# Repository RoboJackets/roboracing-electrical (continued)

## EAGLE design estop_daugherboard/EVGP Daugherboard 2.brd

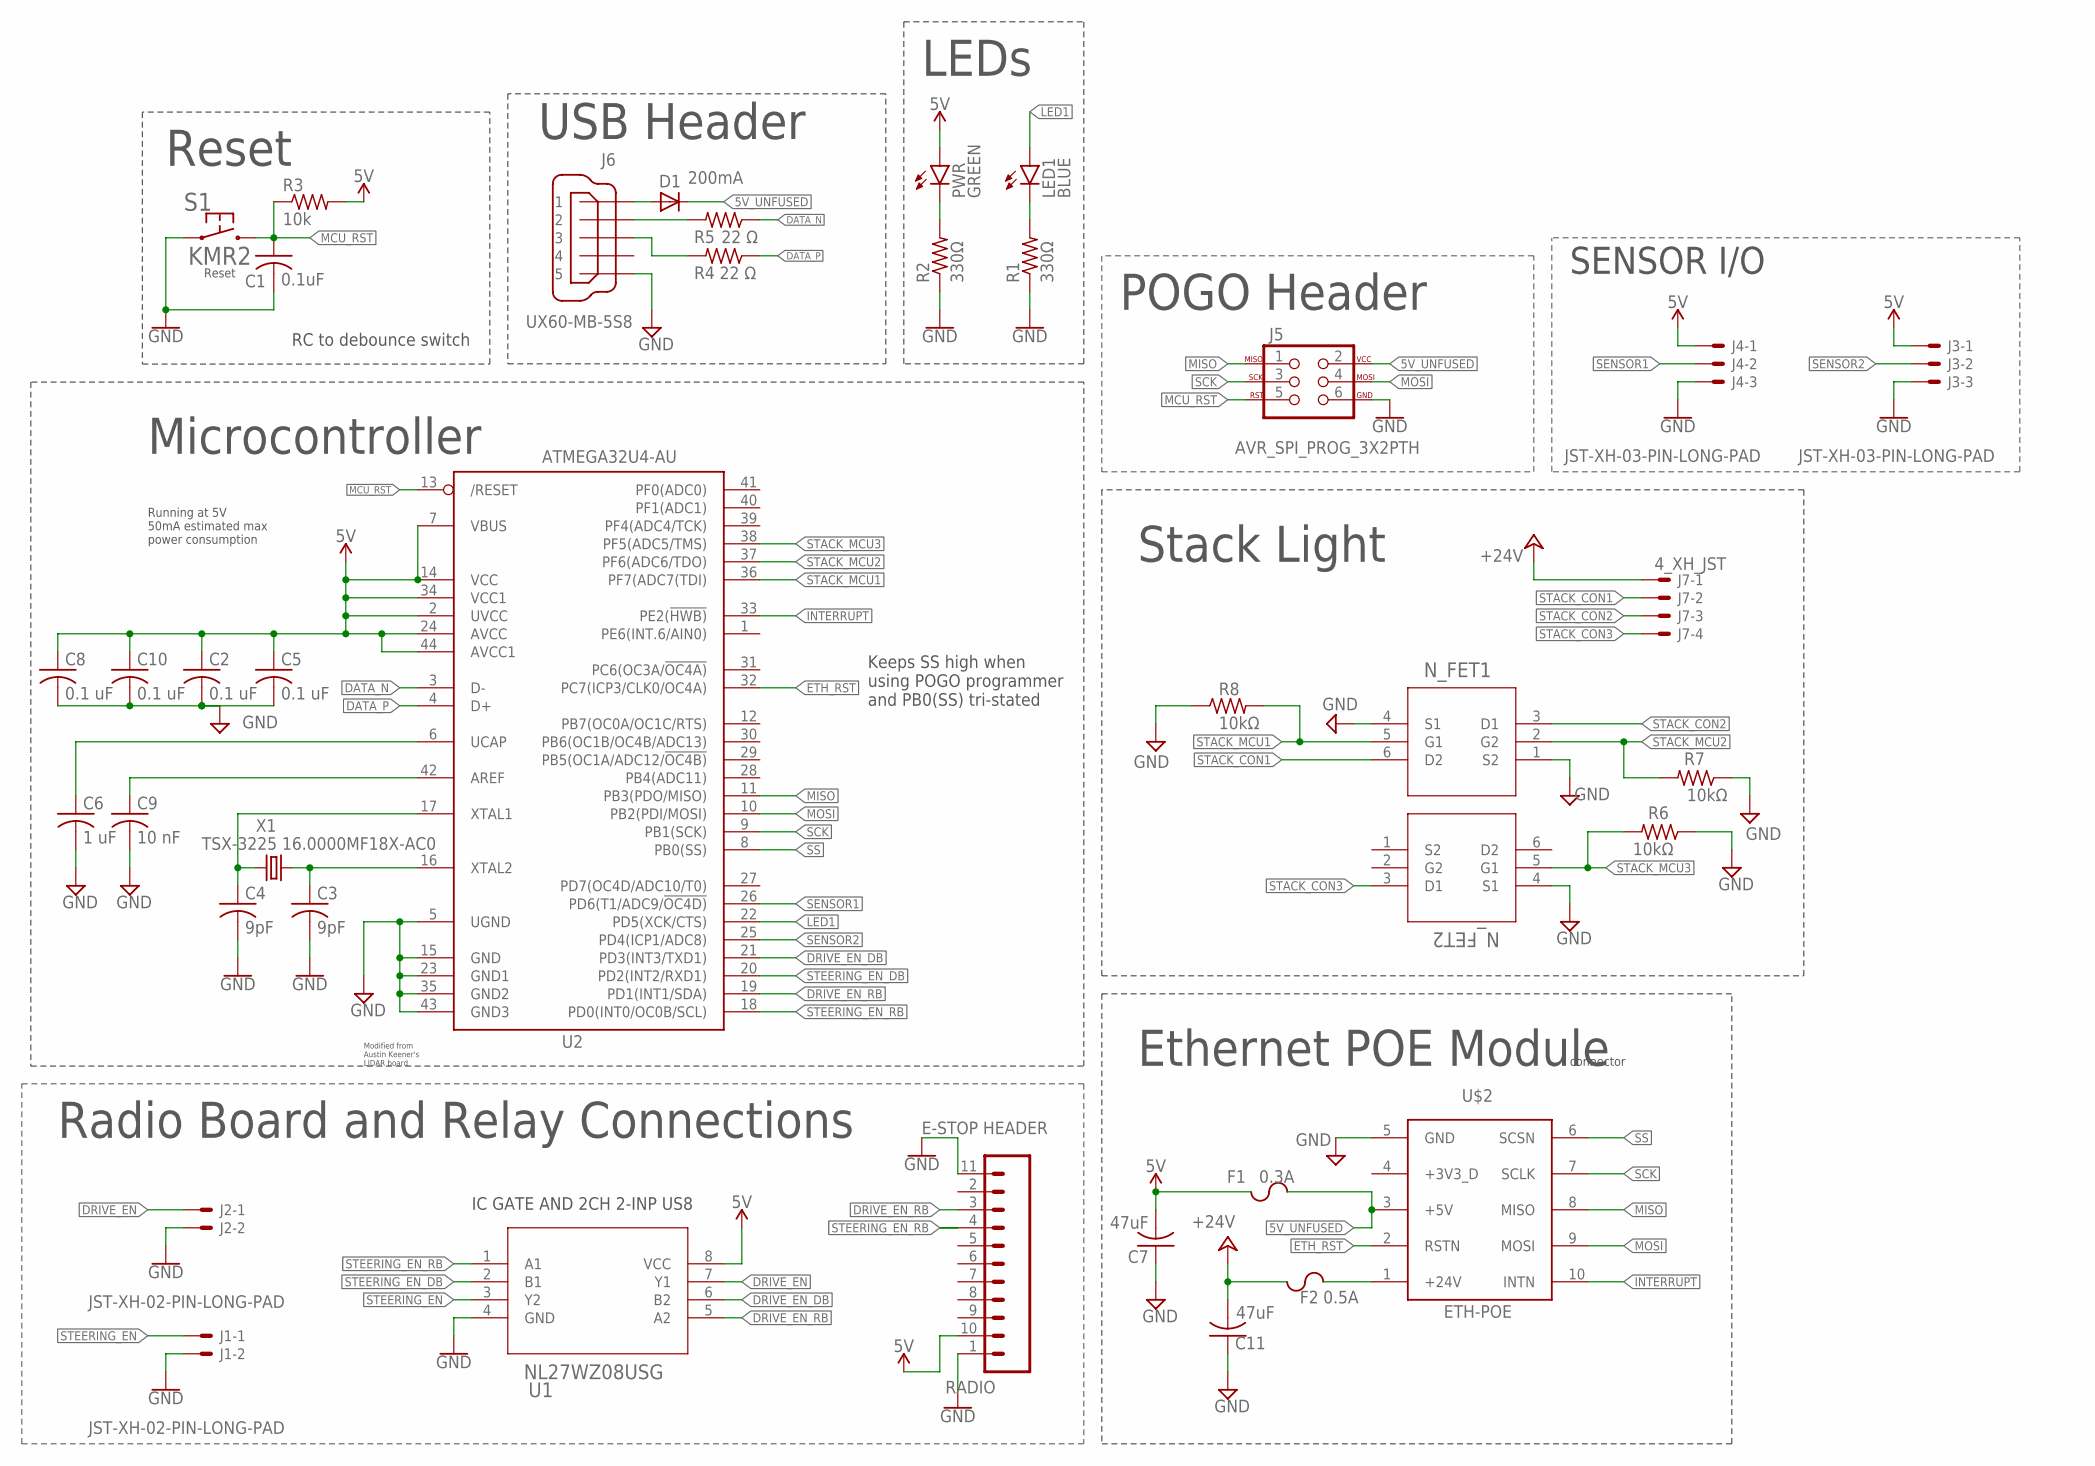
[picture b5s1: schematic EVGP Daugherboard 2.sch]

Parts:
C1: 0.1uF; C0603
C2, C5, C8, C10: 0.1 uF; C0603
C3, C4: 9pF; C0603
C6: 1 uF; C0603
C7, C11: 47uF; C1206
C9: 10 nF; C0603
D1: 200mA; SOD323-R
F1: 0.3A; F1206
F2: 0.5A; F1206
J1, J2: JST-XH-02-PIN-LONG-PAD; JST-XH-02-PACKAGE-LONG-PAD
J3, J4: JST-XH-03-PIN-LONG-PAD; JST-XH-03-PACKAGE-LONG-PAD
J5: AVR_SPI_PROG_3X2PTH; 2X3
J6: UX60-MB-5S8
J7: 4_XH_JST; JST-XH-04-PACKAGE-LONG-PAD
LED1: BLUE; CHIP-LED0603
PWR: GREEN; CHIP-LED0603
Q1: N_FET2; SOT-363
Q2: N_FET1; SOT-363
R1, R2: 330Ω; R0603
R3: 10k; R0603
R4, R5: 22 Ω; R0603
R6, R7, R8: 10kΩ; R0603
RADIO: E-STOP HEADER; RADIO_V1.3
S1: KMR2
U1: NL27WZ08USG; US8_2P40X2P10
U2: ATMEGA32U4-AU; TQFP44
U$2: ETH-POE; HDRVR10W64P4000X254_2X5_1016X508X254B
X1: TSX-3225 16.0000MF18X-AC0; XTAL-3.2X2.5

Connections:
5V: C2.1, C5.1, C7.2, C8.1, C10.1, F1.1, J3.1, J4.1, PWR.A, R3.2, RADIO.10 (5V), U1.8 (VCC), U2.2 (UVCC), U2.7 (VBUS), U2.14 (VCC), U2.24 (AVCC), U2.34 (VCC1), U2.44 (AVCC1)
5V_UNFUSED: D1.C, F1.2, J5.2, U$2.3 (+5V)
24V_UNFUSED: F2.2, U$2.1 (+24V)
+24V: C11.2, F2.1, J7.1
AREF: C9.1, U2.42 (AREF)
DATA_N: R5.1, U2.3 (D-)
DATA_P: R4.1, U2.4 (D+)
DRIVE_EN: J2.1, U1.7 (Y1)
DRIVE_EN_DB: U1.6 (B2), U2.21 (PD3(INT3/TXD1))
DRIVE_EN_RB: RADIO.3 (D1), U1.5 (A2), U2.19 (PD1(INT1/SDA))
ETH_RST: U2.32 (PC7(ICP3/CLK0/OC4A)), U$2.2 (RSTN)
GND: C1.2, C2.2, C3.2, C4.2, C5.2, C6.2, C7.1, C8.2, C9.2, C10.2, C11.1, J1.2, J2.2, J3.3, J4.3, J5.6, J6.5, Q1.4 (S1), Q2.1 (S2), Q2.4 (S1), R1.1, R2.1, R6.1, R7.1, R8.1, RADIO.1 (GND), RADIO.11 (GND), S1.1.1 (1), S1.1.2 (1), U1.4 (GND), U2.5 (UGND), U2.15 (GND), U2.23 (GND1), U2.35 (GND2), U2.43 (GND3), U$2.5 (GND)
INTERRUPT: U2.33 (PE2(!HWB)), U$2.10 (INTN)
LED1: LED1.A, U2.22 (PD5(XCK/CTS))
MCU_RST: C1.1, J5.5, R3.1, S1.2.1 (2), S1.2.2 (2), U2.13 (/RESET)
MISO: J5.1, U2.11 (PB3(PDO/MISO)), U$2.8 (MISO)
MOSI: J5.4, U2.10 (PB2(PDI/MOSI)), U$2.9 (MOSI)
unnamed: PWR.C, R2.2
unnamed: J6.2, R5.2
unnamed: LED1.C, R1.2
unnamed: D1.A, J6.1
unnamed: J6.3, R4.2
SCK: J5.3, U2.9 (PB1(SCK)), U$2.7 (SCLK)
SENSOR1: J4.2, U2.26 (PD6(T1/ADC9/!OC4D))
SENSOR2: J3.2, U2.25 (PD4(ICP1/ADC8))
SS: U2.8 (PB0(SS)), U$2.6 (SCSN)
STACK_CON1: J7.2, Q2.6 (D2)
STACK_CON2: J7.3, Q2.3 (D1)
STACK_CON3: J7.4, Q1.3 (D1)
STACK_MCU1: Q2.5 (G1), R8.2, U2.36 (PF7(ADC7(TDI))
STACK_MCU2: Q2.2 (G2), R7.2, U2.37 (PF6(ADC6/TDO))
STACK_MCU3: Q1.5 (G1), R6.2, U2.38 (PF5(ADC5/TMS))
STEERING_EN: J1.1, U1.3 (Y2)
STEERING_EN_DB: U1.2 (B1), U2.20 (PD2(INT2/RXD1))
STEERING_EN_RB: RADIO.4 (D2), U1.1 (A1), U2.18 (PD0(INT0/OC0B/SCL))
UCAP: C6.1, U2.6 (UCAP)
XTAL1: C4.1, U2.17 (XTAL1), X1.1
XTAL2: C3.1, U2.16 (XTAL2), X1.3 (2)

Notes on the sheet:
Modified from Austin Keener's LIDAR board
POGO Header
RC to debounce switch
Reset
LEDs
Running at 5V 50mA estimated max power consumption
Microcontroller
USB Header
Keeps SS high when using POGO programmer and PB0(SS) tri-stated
Radio Board and Relay Connections
IC GATE AND 2CH 2-INP US8
SENSOR I/O
Stack Light
Ethernet POE Module
connector

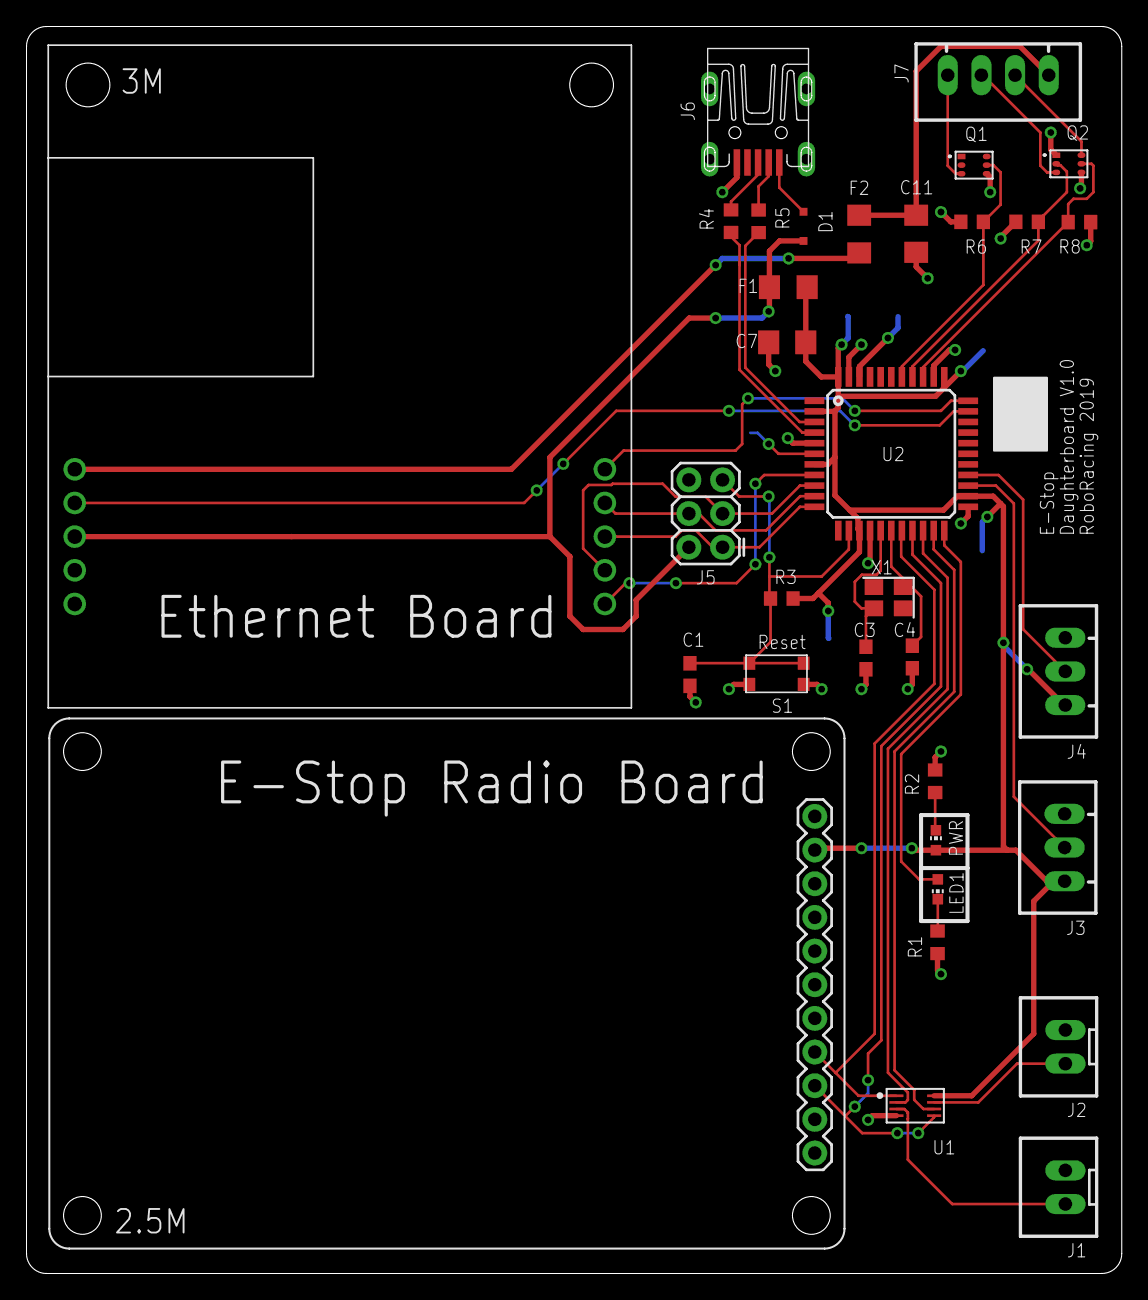
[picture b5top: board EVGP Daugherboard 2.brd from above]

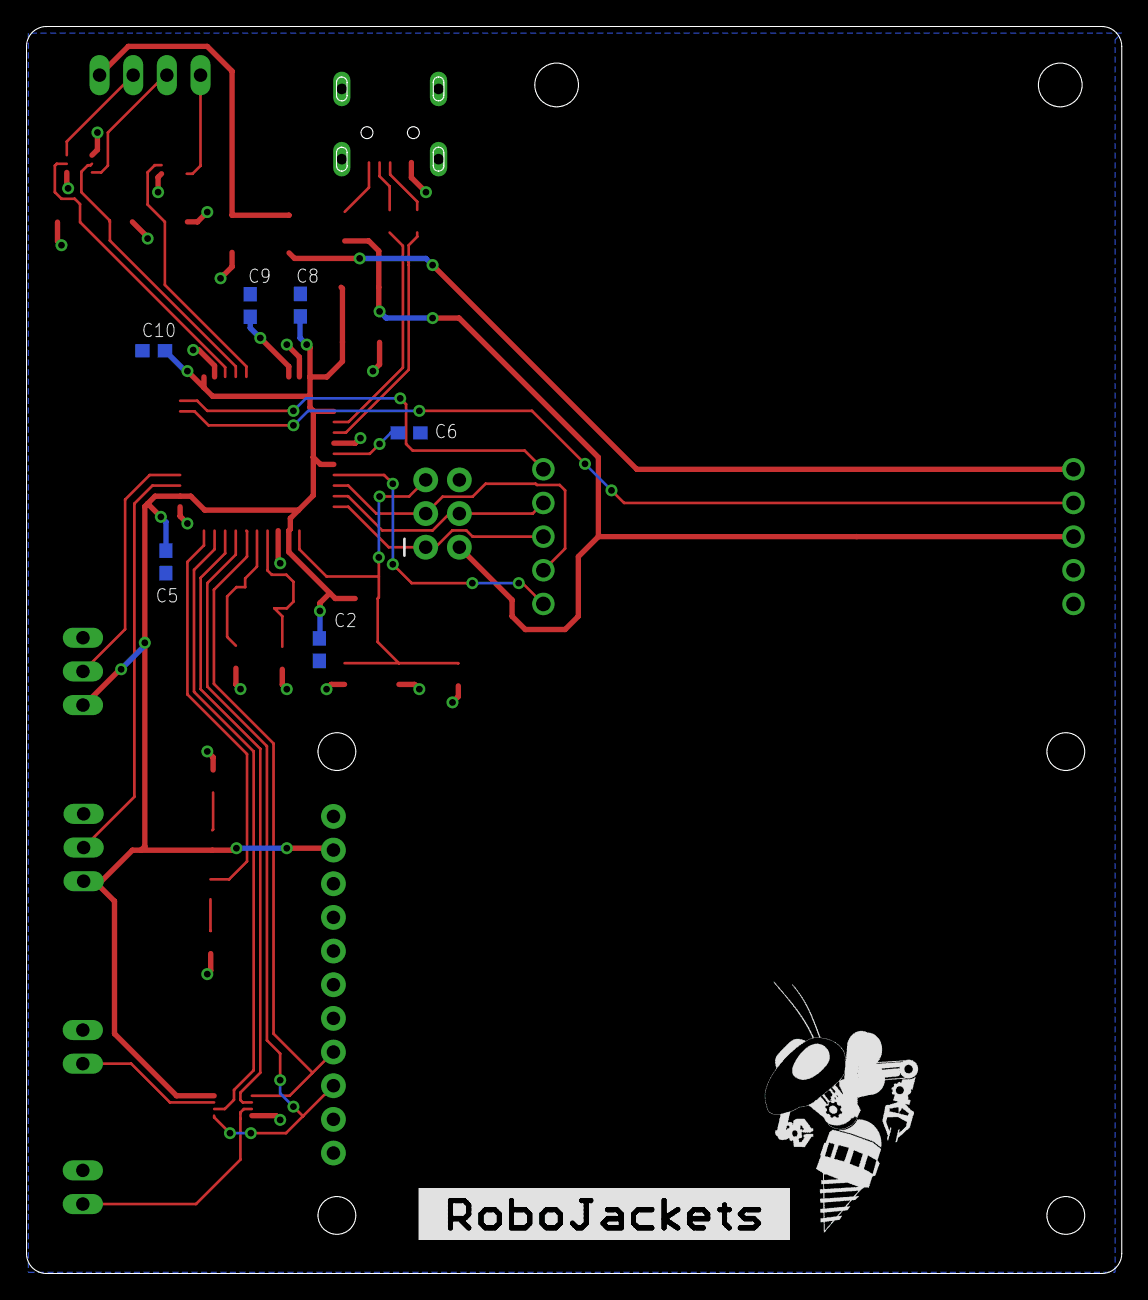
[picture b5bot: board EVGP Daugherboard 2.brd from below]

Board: 2 copper layers, 82.6 x 94.1 mm, 41 parts (8 on the bottom side), 38 nets.

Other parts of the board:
U$1: ROBOBUZZ_1.0X
U$3: ROBOJACKETS
